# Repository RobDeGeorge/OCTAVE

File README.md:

<div align="center">

# OCTAVE

### The car head unit you build yourself.

**Live engine data. Gauges you design on the screen. Music that repaints the whole dash.<br>Your phone on the dash. A black box that remembers every drive.**

<sub>Real app, real UI, recorded from a script. Engine data comes from OCTAVE's built-in car simulator, so you can try all of this with no car.</sub>

**Windows · macOS · Linux · Raspberry Pi / Orange Pi · Android · your browser**

**Try it in your browser: https://robdegeorge.com/OCTAVE/** (the simulated car, no install, about 25 MB)

### [Download](https://github.com/RobDeGeorge/OCTAVE/releases/latest) &nbsp;·&nbsp; [Wiki](https://robdegeorge.com/OCTAVE/wiki/) &nbsp;·&nbsp; [Build your own frontend](https://robdegeorge.com/OCTAVE/wiki/writing-a-frontend.html) &nbsp;·&nbsp; [Frontend playground](https://robdegeorge.com/OCTAVE/playground.html)

</div>

---

Stock head units are locked boxes. Phone projection hides the car behind your phone. **OCTAVE is a full infotainment system you run on your own hardware**: a Pi behind the dash, a laptop in a project car, an old Android tablet. It reads the car over OBD-II, plays your music, mirrors your phone, and every pixel of it is yours to change.

I daily-drive it in my 2003 Jeep TJ.

> **Getting data from your car:** plug an ELM327 OBD-II adapter (the cheap $15–30 kind) into the port under your dash. Every car sold in the US since 1996 has one.
> - **USB** adapters work on every platform.
> - **Bluetooth** adapters pair from inside OCTAVE on Linux and the Pi. On Windows and macOS, pair it in system settings and pick its port.
> - **BLE** adapters work on Android.
>
> No car handy? `octave --sim` drives a simulated one, in any build.
>
> I am also designing an adapter for OCTAVE itself, every OBD-II protocol on one board: [an OBD adapter of its own](#an-obd-adapter-of-its-own). It is not built yet.

<table>
<tr>
<td width="33%" align="center"><br><b>Music paints the dash</b><br><sub>Every song recolours the UI</sub></td>
<td width="33%" align="center"><br><b>Gauges you design</b><br><sub>On the screen or in a browser, 129 live readings</sub></td>
<td width="33%" align="center"><br><b>A black box</b><br><sub>Every drive recorded, charted and compared</sub></td>
</tr>
<tr>
<td align="center"><br><b>Your phone on the dash</b><br><sub>Android over USB or Wi-Fi, iPhone over AirPlay</sub></td>
<td align="center"><br><b>Shift light & codes</b><br><sub>Read and clear the check-engine light</sub></td>
<td align="center"><br><b>Open API</b><br><sub>Drive it from a browser or a script</sub></td>
</tr>
<tr>
<td align="center"><br><b>The car in 3D</b><br><sub>Doors, lights and tilt, live</sub></td>
<td align="center"><br><b>Your own screen</b><br><sub>Swap the whole UI for one you wrote</sub></td>
<td align="center"><br><b>Its own OBD adapter</b><br><sub>Designed here, not built yet</sub></td>
</tr>
</table>

---

## Music that paints the whole dash

Skip a track and the whole interface takes its colours from the cover art. Local MP3, M4A and FLAC with a live waveform.

## Gauges you design on the screen

**129 live readings** (121 OBD-II PIDs plus the IMU), **13 widget types**, and full-screen dashboards you swipe between. Pick one of the built-ins or build your own:

No code and no JSON. Start from a template that fills itself in with what your car reports, then select a gauge and drag it: the others move out of the way. The gallery shows every widget running on live data, the picker lists your car's readings by system, and one sheet per gauge covers its look, range and warning limits, with a test value to watch them trip. Undo, redo, three grid densities, and a portrait layout of its own. Share a dashboard as a file or through the clipboard.

Rather use a keyboard? The head unit serves the same editor to a browser (**Dashboards > In a browser** shows the address, a QR code and a pairing code), and what you change there previews live on the car's screen:

A dashboard can also watch the car for you: a red strip across the top when one of its values goes critical, or a rule that brings it up by itself, such as the temperatures when the coolant runs hot.

Screen mounted upright, or running on a phone? Home and every dashboard re-flow for portrait.

<p align="center">
  
  &nbsp;&nbsp;
  
</p>

## A black box for every drive

OCTAVE records **every reading of every drive**, quietly, in the background. Open Trip History to see each drive's distance, top speed, peak coolant, voltage and fuel used, and chart any parameter over the whole trip. Export a drive as CSV, or open the files yourself.

**Trends** lines your drives up against each other: warm-up time, running coolant temperature, idle and charging voltage, warm idle speed, fuel trims. When the recent drives move away from the earlier ones it says so, and what usually causes it. Here a thermostat is starting to stick open.

<sub>The history in these pictures is generated (`tools/trips/make_mock_trip.py`): 40 drives over two months with a thermostat wearing out.</sub>

## Shift light, warnings and trouble codes

Set your own RPM bands: the lamp goes green, flashes yellow, and at the top **the whole screen strobes red**, whatever page you're on. Any gauge can also be a warning light with its own threshold.

Check-engine light on? Read the stored and pending codes in plain English, grab the freeze frame, and clear them, right from the dash.

## Your phone on the dash

Plug in an Android phone, or pair it once over Wi-Fi by scanning a QR code. OCTAVE mirrors a DeX-style desktop onto the dash with its own built-in client: **nothing to install on the phone**. A bumped USB cable picks up where it left off instead of starting over.

**iPhone:** OCTAVE is an AirPlay receiver, so an iPhone mirrors its screen or plays its music to the dash the way it would to an Apple TV. AirPlay carries no touch, so the head unit also pairs with the phone as a Bluetooth mouse and your taps on the dash land on the phone. Linux and the Pi for now, and off until you turn it on.

**Android Auto** runs through Google's Desktop Head Unit, or through OCTAVE's own built-in receiver (beta, checked on desktop Linux so far).

## The car, live in 3D

A rigged model of the Jeep with working doors, hood, tailgate, lights, steering and wheels, rolled and pitched in real time by an IMU on the dash.

Pitch, roll, heading, a G-force plot with a trail, altitude and temperature, sampled at 200 Hz.

## Drive it from anything

<table>
<tr>
<td width="38%" align="center"></td>
<td>

Everything the touch screen can do is open to other programs over a small JSON API. Start OCTAVE with `--service --service-bind 0.0.0.0` and open **`http://<head-unit-ip>:9876/`** on your phone, enter the pairing code from Settings > Device > Service: live gauges, now playing, volume. Or run it with **no screen at all** (`--headless`) and make your own UI.

```python
from octave_client import Client

with Client() as octave:
    octave.call("nowPlaying", "next")
    octave.subscribe("paramStore", properties=["RPM", "SPEED"])
    for event in octave.events():
        print(event["values"])        # {'RPM': 2210, 'SPEED': 41}
```

[SDKs](sdk/) for Python, TypeScript and Go, a no-build [web client](sdk/web/index.html), [starter projects](templates/) to copy, the full [API reference](https://robdegeorge.com/OCTAVE/wiki/api-reference.html), and a walkthrough: **[Writing a Frontend](https://robdegeorge.com/OCTAVE/wiki/writing-a-frontend.html)**. Install your frontend as the head unit's screen from Settings > Device > Frontends; *Try* gives it two minutes, and five presses of mute always bring the built-in screen back.

**[Try a frontend in your browser](https://robdegeorge.com/OCTAVE/playground.html)** against the real core and a simulated car, or browse the **[frontend gallery](https://robdegeorge.com/OCTAVE/wiki/frontend-gallery.html)**: five complete examples in Svelte, Textual, Gio, SDL2 and egui (`examples/frontends/`, MIT). Built one? See [CONTRIBUTING.md](CONTRIBUTING.md).

</td>
</tr>
</table>

<p align="center"><sub>The five example frontends: Glass (Svelte), Sunlight (Go + Gio), Retro Cluster (Rust + egui), Arcade (C + SDL2), Console (Python + Textual). Each one is a complete screen for the same car.</sub></p>

## An OBD adapter of its own

The $20 ELM327 clones work, and they are the slow part of the system: every reading waits for a Bluetooth round trip, and they keep drawing current from a parked car. So OCTAVE is getting an adapter of its own, designed in this repository: [`hardware/obd-adapter/`](hardware/obd-adapter/).

- **Every OBD-II bus on one board:** two CAN channels, K-line (ISO 9141 / KWP2000) and J1850 VPW / PWM for older Chrysler, GM and Ford cars. My 2003 TJ speaks VPW, which a CAN-only dongle cannot hear at all.
- **An STM32G474 on the car's side, an ESP32 for the radio:** Bluetooth Classic, BLE and Wi-Fi, plus USB-C for a head unit on a cable.
- **Plugs straight into the port,** on a small J1962 plug board soldered across its end. Reverse-battery and surge protection on the way in; the supply is simulated to keep running through a 6 V cold crank.
- **Meant to do more than an ELM327.** The plan is the ELM327 command set for every app, plus a native mode: the adapter schedules the polling itself, stamps each sample as it comes off the bus, and keeps recording while Bluetooth is down, to fill the black box in afterwards.
- **A board written as code.** The schematic, placement, routing and fab files are generated by Python ([`gen/obd_adapter.py`](hardware/obd-adapter/gen/obd_adapter.py) is the design; `python3 build.py all` rebuilds everything through KiCad and Freerouting), and checked the same way: ERC and DRC clean, the STM32's pins against ST's own data, two datasheet audits, and ngspice simulations of the supply, the input protection and the K-line and J1850 circuits. Every finding and what was done about it is in [`verify/REVIEW.md`](hardware/obd-adapter/verify/REVIEW.md).

> **Where it stands:** Rev 0 is a bring-up board for the bench and the Jeep, not the final dongle. It is designed and routed, the fab files are generated, and bring-up firmware is started (it builds and passes its host tests; it has never run on hardware). **Nobody else has reviewed the board, and it has not been ordered or built.** Read it, learn from it, tell me what is wrong with it, but do not send it to a fab yet. Plan and background: [`TODO/diy-obd-adapter.md`](TODO/diy-obd-adapter.md). Nothing in OCTAVE depends on it: the ELM327 adapters above keep working.

---

## Install

Grab the file for your platform from **[Releases](https://github.com/RobDeGeorge/OCTAVE/releases/latest)**. No toolchain needed.

| Platform | File | |
|---|---|---|
| Windows | `OCTAVE-<version>-windows-x86_64.exe` | Run the installer |
| macOS | `OCTAVE-<version>-macos.dmg` | Drag to Applications |
| Linux | `OCTAVE-<version>-linux-x86_64.AppImage` | `chmod +x`, then run |
| Raspberry Pi / Orange Pi (64-bit) | `OCTAVE-<version>-linux-aarch64.AppImage` | `chmod +x`, then run |
| Android | `OCTAVE-<version>-android-arm64-v8a.apk` | Sideload it |

<details>
<summary>Platform notes</summary>

- **Linux:** Ubuntu 22.04+, Debian, Mint, Fedora, openSUSE and Arch. Arch may need `sudo pacman -S fuse2`, or run `./OCTAVE-*.AppImage --appimage-extract-and-run`.
- **Android:** each release APK is signed with its own key, so uninstall the previous version before updating.

</details>

## How it compares

| | OCTAVE | Crankshaft | OpenAuto Pro | Stock Android Auto |
|---|---|---|---|---|
| Open source | Yes, GPLv3 | Yes | partial | No |
| Works without a phone | Yes | No, AA projection | No, AA projection | No |
| Live OBD-II, your own dashboards | Yes | No | limited | No |
| Records every drive | Yes | No | No | No |
| Phone mirroring | Yes: Android with nothing to install, iPhone over AirPlay | AA only | AA only | n/a |
| Open API for your own UI | Yes | No | No | No |
| Fully themable / forkable UI | Yes, QML | limited | limited | No |
| Develop on your laptop | Yes, Win / macOS / Linux | Pi only | Pi only | n/a |

## Everything else it does

- **ESP32 wireless volume knob** with an LED ring that matches the theme
- **Gesture sensor** (PAJ7620U2): wave to skip, pause or change the volume
- **Bluetooth OBD adapters** found, paired and connected from the app on Linux; BLE adapters on Android
- **Spotify** (experimental): your playlists in the same song table as your own music, playing on the Spotify app on your phone (Premium)
- **Pick the audio output**: the car's amp, a USB DAC or Bluetooth, from Settings
- **The browser demo is the real app**: point it at a folder of your own music, or connect a real Bluetooth LE adapter from Chrome or Edge
- **100+ settings**, all on the screen, all saved
- **The whole wiki inside the app**, readable offline
- **Logs and crash traces** you can export from the dash when something goes wrong

---

## Hack on it

OCTAVE is C++ / Qt 6 with a QML frontend, built with CMake, small enough to fork. `--dev` runs it with a **simulated car** (warm-up, overheating and low-fuel scenarios) and simulated motion, so you can work on gauges at your desk.

<details>
<summary><b>Build from source</b></summary>

Qt 6.7+ and CMake 3.21+:

```bash
git clone https://github.com/RobDeGeorge/OCTAVE.git
cd OCTAVE
cmake -S . -B build -DCMAKE_BUILD_TYPE=Debug
cmake --build build -j8
./build/octave --dev                       # with the simulated car
ctest --test-dir build --output-on-failure # the test suite
```

Every platform and packaging target is in [BUILD.md](BUILD.md). The optional Python tools around the app (dev scripts, docs builders) install into a virtualenv next to the checkout:

```bash
python3 -m venv venv && venv/bin/pip install -r requirements.txt
```

Until October 2026 OCTAVE also had a Python / PySide6 backend. It is frozen, with its own wiki, on the [`python-final`](https://github.com/RobDeGeorge/OCTAVE/tree/python-final) branch.

</details>

<details>
<summary><b>Dev tooling: how the clips above were made</b></summary>

Every clip and picture in this README is scripted, and one command makes them all again. `./build/octave --dev --profile` (a Debug build) runs OCTAVE with the simulator and a local command server; a story script drives it scene by scene (navigate, play, floor the throttle, tap buttons by their label, type into fields, build a dashboard), captures the window from inside Qt, and writes WebP and PNG. The same run fills the black box with two months of mock drives, shoots the browser pages in headless Chromium, renders the adapter board with `kicad-cli` from the committed design, and then checks that every picture this file points at exists. The same channel is exposed as MCP tools, so a coding agent can drive the app, change settings, read performance counters and record clips. The in-app half is in `src/dev/`; see the [Development guide](https://robdegeorge.com/OCTAVE/wiki/development.html).

</details>

## What's next

- **The OBD adapter as a real board**: a review, a first order, and the firmware on hardware ([plan](TODO/diy-obd-adapter.md))
- **Android on the Play Store**: the APK runs today as a sideload ([plan](TODO/android-cpp-port.md))
- **Wireless CarPlay / Android Auto** through a CarlinKit dongle ([plan](TODO/carlinkit-dongle-port.md))
- **Video over the API**, so your own frontend can show the phone mirror too ([plan](TODO/open-backend.md))

Every plan lives in [`TODO/`](TODO/).

## Documentation

The **[wiki](https://robdegeorge.com/OCTAVE/wiki/)** covers the architecture, every manager and page, every setting, hardware setup and the build guides. The same pages ship in [`wiki/`](wiki/index.html) and inside the app. Building gauges: [`docs/GAUGE_AUTHORING.md`](docs/GAUGE_AUTHORING.md). Building a frontend: [Writing a Frontend](https://robdegeorge.com/OCTAVE/wiki/writing-a-frontend.html) and [`docs/api/`](docs/api/README.md).

## Contributing

Pull requests and bug reports are welcome. Built a dashboard, a sensor integration, a port to new hardware, or your own frontend? Open an issue or a PR. I'd love to see it.

<details>
<summary><b>Built with</b></summary>

OCTAVE stands on a lot of other people's work.

**C++ app (every release binary)**

| Library | Used for |
|---|---|
| [Qt 6](https://www.qt.io/) (Core, Gui, Qml, Quick, Quick Controls 2, Multimedia, Network, Concurrent, SerialPort, Bluetooth) | The whole application: UI, audio playback, networking, serial and Bluetooth OBD |
| Qt Quick 3D, Quick 3D Asset Utils, Quick Timeline | The 3D Jeep and the music-device scenes |
| Qt DBus | BlueZ pairing on Linux |
| Qt WebEngine / Qt WebView | The offline wiki reader (desktop / Android) |
| Qt Sensors | The phone's motion sensors on Android |
| [TagLib](https://taglib.org/) | Reading tags and embedded album art |
| [FFmpeg](https://ffmpeg.org/) (libavcodec, libavutil) | Decoding the phone mirror's H.264 stream |
| [SQLite](https://sqlite.org/) | The black box (compiled in from `third_party/sqlite/`) |
| [OpenSSL](https://www.openssl.org/) | The built-in Android Auto receiver's encryption; the AirPlay receiver |
| [libplist](https://libimobiledevice.org/) | The AirPlay receiver (Linux), with FFmpeg and OpenSSL |
| [CMake](https://cmake.org/) | Build system |

**Python helper tools (optional, `requirements.txt`)**

| Package | Used for |
|---|---|
| [MCP Python SDK](https://github.com/modelcontextprotocol/python-sdk), [Pillow](https://python-pillow.org/), [mss](https://github.com/BoboTiG/python-mss), [NumPy](https://numpy.org/), [psutil](https://github.com/giampaolo/psutil) | Dev tooling: MCP servers, screenshots and clips, perf scripts |
| [python-OBD](https://github.com/brendan-w/python-OBD) | Dev scripts for reading and clearing trouble codes |
| [Ruff](https://docs.astral.sh/ruff/) | Lint |

**Android**

| Library | Used for |
|---|---|
| Qt for Android, Gradle, Android SDK / NDK | Building the APK |
| [OpenSSL](https://www.openssl.org/) | HTTPS for Qt Network (`android/openssl/`) |

**Code bundled in this repository**

| Component | License | Where |
|---|---|---|
| [scrcpy](https://github.com/Genymobile/scrcpy) server, forked at v3.3.4 | Apache 2.0 | `phone_server/`, prebuilt jar in `tools/phone-server/` |
| [UxPlay](https://github.com/FDH2/UxPlay)'s AirPlay library, 1.74 | LGPL 2.1+, with GPL 3.0 and MIT parts (see its README) | `third_party/uxplay/` |
| [QR Code generator library](https://www.nayuki.io/page/qr-code-generator-library) by Project Nayuki | MIT | `src/phone_mirror/qrcodegen.*` |
| Android platform-tools (`adb`) | See its `NOTICE.txt` | `tools/platform-tools/` |

**External tools and services:** adb (phone mirroring and Android Auto), Google's Android Auto Desktop Head Unit (the Android Auto view).

**The OBD adapter (`hardware/obd-adapter/`):** [KiCad](https://www.kicad.org/) (the project, `kicad-cli` checks, fab output and the renders above), [Freerouting](https://github.com/freerouting/freerouting) (autorouting), [ngspice](https://ngspice.sourceforge.io/) (simulations), `arm-none-eabi-gcc` (firmware).

**Fonts, icons and 3D assets**

- **[Google Sans](https://fonts.google.com/)**: UI typeface. **[JetBrains Mono](https://www.jetbrains.com/lp/mono/)**: monospace readouts.
- **OCTAVE Symbols**: a subset of [Noto Sans Symbols and Noto Sans Symbols 2](https://fonts.google.com/noto) (SIL OFL), renamed as the OFL requires, built by `tools/fonts/build_symbol_font.py` with [fontTools](https://github.com/fonttools/fonttools).
- **Icons**: original SVGs drawn for OCTAVE (Illustrator sources in `frontend/assets/-src/`).
- **The 2003 Jeep TJ**: an original model, built procedurally in [Blender](https://www.blender.org/) by `tools/vehicle/build_jeep_tj.py` from photos of one real TJ; no third-party meshes or textures ([details](tools/vehicle/README.md)).
- **Record player, cassette deck, CD player, iPod and friends**: original glTF models generated by `tools/music_devices/generate.py` (NumPy, Pillow).
- **Studio lighting (`.hdr`)**: generated by `tools/vehicle/build_studio_probe.py`.

**CI and packaging:** [GitHub Actions](https://github.com/features/actions) with [install-qt-action](https://github.com/jurplel/install-qt-action), [setup-android](https://github.com/android-actions/setup-android) and [action-gh-release](https://github.com/softprops/action-gh-release); [vcpkg](https://vcpkg.io/) and [Homebrew](https://brew.sh/) for TagLib and FFmpeg; [Inno Setup](https://jrsoftware.org/isinfo.php) for the Windows installer; [linuxdeploy](https://github.com/linuxdeploy/linuxdeploy) with its Qt plugin for the AppImages; `windeployqt`, `macdeployqt` and `androiddeployqt` from Qt.

</details>

## License

Copyright 2026 Rob DeGeorge.

OCTAVE is free software: you can redistribute it and/or modify it under the terms of the GNU General Public License as published by the Free Software Foundation, either version 3 of the License, or (at your option) any later version. It is distributed in the hope that it will be useful, but WITHOUT ANY WARRANTY; without even the implied warranty of MERCHANTABILITY or FITNESS FOR A PARTICULAR PURPOSE. See [LICENSE](LICENSE) for the full text.

The service clients (`sdk/`), starter projects (`templates/`) and example frontends (`examples/frontends/`) are MIT, so a frontend you build on them can use any license ([Your Frontend, Your License](wiki/writing-a-frontend.html#license)).

Code published before 2026-10-12 (v0.9.4 and earlier) was released under the MIT License and remains available under those terms.

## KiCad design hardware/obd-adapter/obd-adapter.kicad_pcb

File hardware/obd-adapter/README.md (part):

# OCTAVE OBD adapter, Rev 0 (bring-up board)

Our own OBD-II adapter: STM32G474 (vehicle side) + ESP32 (Bluetooth Classic SPP, BLE, Wi-Fi), every OBD-II bus, USB-C. Rev 0 is a bring-up board for the bench and the Jeep, not the final dongle. It has room to probe, test points and header access to spare pins, and it plugs straight into the car's OBD-II port. Plan and background: `TODO/diy-obd-adapter.md`.

**Status:** generated, then verified: an STM32 pin check against ST's pin data, two independent datasheet audits and ngspice simulations. Every finding is fixed or accepted, see `verify/REVIEW.md`. Not yet reviewed by a human, not ordered. Read "Before ordering" below.

**The main board is routed** (2026-11-10): 0 DRC errors, 0 unconnected pads, schematic and board agree. `gen/routing.json`, `obd-adapter.kicad_pcb`, `drc.rpt` and everything in `fab/` are that board, with the changes of 2026-11-09 in it (the buck loop, the parked-watch parts, the microSD, the mounting holes, `verify/REVIEW.md` rounds 5 to 7). The route is the autorouter's, finished by hand round the STM32; it has passed the rule check, not a person's eye. Later the same day (`verify/REVIEW.md` round 8): the crystal's tracks and the CAN1 pair were re-laid by hand, and six BOM lines moved to parts from JLCPCB's no-fee libraries, which changed four values round the buck (RT 160k, feedback 68k / 12k, 47 pF on COMP).

## Files

| Path | What |
|---|---|
| `gen/obd_adapter.py` | **The design.** Every part, its LCSC number and its pin-to-net map. Edit this, not the KiCad files. |
| `gen/parts.py` | LCSC part numbers, checked against JLCPCB's parts library on 2026-11-02, 2026-11-09 and 2026-11-10. |
| `gen/layout.py` | Board placement: fixed positions for the parts whose position matters, block regions for the rest. |
| `gen/libdefs.py` | Project symbols KiCad doesn't ship (SOIC-8 N-MOSFET, TPS22918, CH340C, LIS2DH12), with the pinouts checked against the datasheets, and the two plug footprints (drawn by `gen/mklib.py`). |
| `gen/build.py` | Regenerates everything (see below). |
| `obd-adapter.kicad_sch` / `.kicad_pcb` | Generated KiCad 10 project. Open it in KiCad to review. |
| `gen/plugprint.py` | Draws the 1:1 print of the plug's adapter board from its `.kicad_pcb` (run by `build.py fab`). |
| `fab/` | Generated: Gerber zips, JLCPCB BOM + CPL, hand-fit list, and `obd-adapter-plug-rev0-print-1to1.pdf`, the sheet to try a bought plug on. |
| `firmware/` | Bring-up firmware for the STM32 (bare-metal C, CMake + `arm-none-eabi-gcc`): reset-safe pins, clock, a serial console, battery voltage, I2C scan, CAN listen-only, K-line. Builds for the board and for a NUCLEO-G474RE; **not yet run on hardware**. See `firmware/README.md`. |
| `verify/` | Pre-fab verification: `REVIEW.md` (every finding and its fix), the STM32 pin check, the ngspice sims and plots. |

```bash
cd hardware/obd-adapter/gen
python3 build.py sch      # project symbols, schematic, ERC (kicad-cli)
python3 build.py pcb      # board with placement (pcbnew Python API)
python3 build.py route    # Freerouting autoroute, GND pours, DRC with schematic parity
python3 build.py fab      # Gerbers, drill, BOM, CPL
python3 build.py all
```

Use the system `python3` (KiCad's `pcbnew` module lives there), not the repo venv. Tools: KiCad 10, Java, and the Freerouting 2.5 jar (`~/.local/share/freerouting/freerouting-2.5.0.jar`, or set `FREEROUTING_JAR`). 2.2 loops forever on this board.

`build.py route` replays the frozen routing (`gen/routing.json`) and refuses if parts moved. To route again:

- `OBD_REROUTE=patch python3 build.py route`: keeps the frozen routing, drops only the copper over parts that moved (or in a DRC clash) and routes the gaps. Minutes, for small placement changes.
- `OBD_REROUTE=1 python3 build.py route`: a full route from scratch. About 4 hours for the board as it is now, and it will not finish by itself: see "How the board is routed" before throwing the frozen route away.

Before a full route, check the placement in seconds: `python3 precheck.py` (DRC with the hand-laid power copper in place) and `python3 congestion.py` (a routing-density estimate; keep `peak` ≤ 0.55 and `p95` ≤ 0.33, the levels this board has routed clean at). `OBD_W` / `OBD_H` try another board size, `OBD_TWO_SIDED=1` puts the small parts on the bottom.

The schematic and the board are generated from the same netlist, and `kicad-cli pcb drc --schematic-parity` checks that they agree. Every pin on the schematic is joined by net label, so a net is everything that carries the same name. The sheet (A0) spaces each part by what it really takes up, labels and text included, and `build.py sch` stops if any two pieces of text touch. **Do not hand-edit the generated files**: the next build overwrites them. The exceptions are copper and labels: after routing by hand in KiCad, run `build.py freeze` so the next build replays your tracks, and copy any reference-label moves into `LABELS` in `gen/layout.py`.

## Blocks

**MCU: STM32G474RET6.** A 16 MHz crystal (for FDCAN timing), SWD on a 2x5 1.27 mm header, RESET / USER buttons, R/G/B LEDs and a 4-way `CONFIG` DIP switch (SW6): 1 ESP_ON, 2 / 3 the CAN1 / CAN2 120 Ω terminations, 4 BOOT0. All off in the car. VDDA / VREF+ are on 3V3 with their own 100 nF + 1 µF (no ferrite bead: the ADC only reads the battery divider). The USER button (PA15) and `KLINE_RX` (PC0) have no pull-up resistor; firmware uses the pins' own.

**Power:** J1962 pin 16 → 2 A 60 V PTC (2920L200/60) → 5.0SMDJ26CA → LM74700 ideal diode + AO4264E → `VBAT_P` (with 47 µF bulk).
- `VBAT_P` feeds a TPS54360B buck (60 V input; the datasheet's 600 kHz design with the output set to 5.33 V), then an SS34 diode-OR with USB VBUS (`5V` ≈ 4.9 V), then an AP2114H 3.3 V LDO (SOT-223).
- The buck's EN divider is not fitted, so the internal UVLO keeps it running through a 6 V cold crank. A cycle-by-cycle simulation (`verify/sim/sim_buck_sw.py`, `verify/REVIEW.md` round 8) has `5V_BUCK` unmoved through that crank, regulating down to 5.6 V at the plug, with under 9 mV of ripple from 9 to 42 V and 131 mV of dip on a 0.1 to 1.0 A load step.
- **To check on the first board:** the buck's SW node with 6 to 7 V on the plug and 0.5 to 1 A drawn from 5 V. Alternating pulse widths would mean the part's internal slope compensation (not published) is short for 8.2 µH at that duty cycle; a 10 or 15 µH inductor in the same footprint is the fix (`verify/REVIEW.md` #71).
- The ESP32 has its own TPS22918 load switch, placed at the module's 3V3 pin. Its ON pin is a diode OR of `ESP_PWR_EN` (PB6, off at reset) and `VBUS2` (the ESP32's USB port), so plugging into J7 always powers the ESP32. CONFIG switch 1 (`ESP_ON`) also powers it without STM32 firmware, by pulling the PB6 net to 3V3 through 1k (R70); turn it off again for normal use. Firmware that drives PB6 low with the switch left on wastes 3.3 mA and the ESP32 stays off.
- A 1k bleed (R69) holds `VBUS2` at ground while J7 is unplugged. Without it the reverse leakage of J7's SS34 (up to 0.4 mA in a hot car) raised the load switch's ON pin and the ESP32 switched itself on.
- The ideal diode (U6 LM74700 driving Q1, an AO4264E 60 V FET) blocks a reversed battery and holds `VBAT_P` up through a negative pulse, for about 20 mV where a diode costs 0.3 V. A B560C Schottky in its place was tried on 2026-11-09 (three parts and 80 µA of parked current less) and taken out again: with the battery reversed its leakage pulled `VBAT_P` to −0.7 V at 100 °C, past the buck's −0.3 V rating, and it took 0.3 V off the cranking headroom (`verify/REVIEW.md` #54, `verify/sim/sim_input_d29.py`). The battery-voltage divider is ahead of it, on `VBAT_F`.
- The TVS is bidirectional on purpose. A unidirectional one would conduct into a reversed battery and defeat the ideal diode.
- Everything on `VBAT_P` must survive the TVS's ~42 V clamp.

**DLC_SW:** a switched battery rail (SI2309CDS P-MOSFET high side, `DLC_SW_EN` = PC3). It feeds the J1850 supply, the LM2901 (through 470 Ω and a 33 V zener) and the K/L 510 Ω pull-ups (through 1N4148W, so the car's own pull-up cannot back-feed the rail while it is off). ScanTool's STN datasheets warn that pull-ups left on the battery draw sleep current and can disturb the bus, up to stalling an engine.

**J1850 VPW / PWM:** STN-style discrete circuit, adapted from the STN1110/1170/21xx reference schematics (3.3 V parts like ours).
- **Supply:** LM317L with 240 / 680 / 470 Ω gives 7.24 V for VPW. A 2N7002 on `J1850_VSEL` (PB2) shorts the 470 Ω for 4.79 V (PWM).
- **Bus+:** 2N7002 → AO3401A → Schottky, with a 10k + Schottky bus load.
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
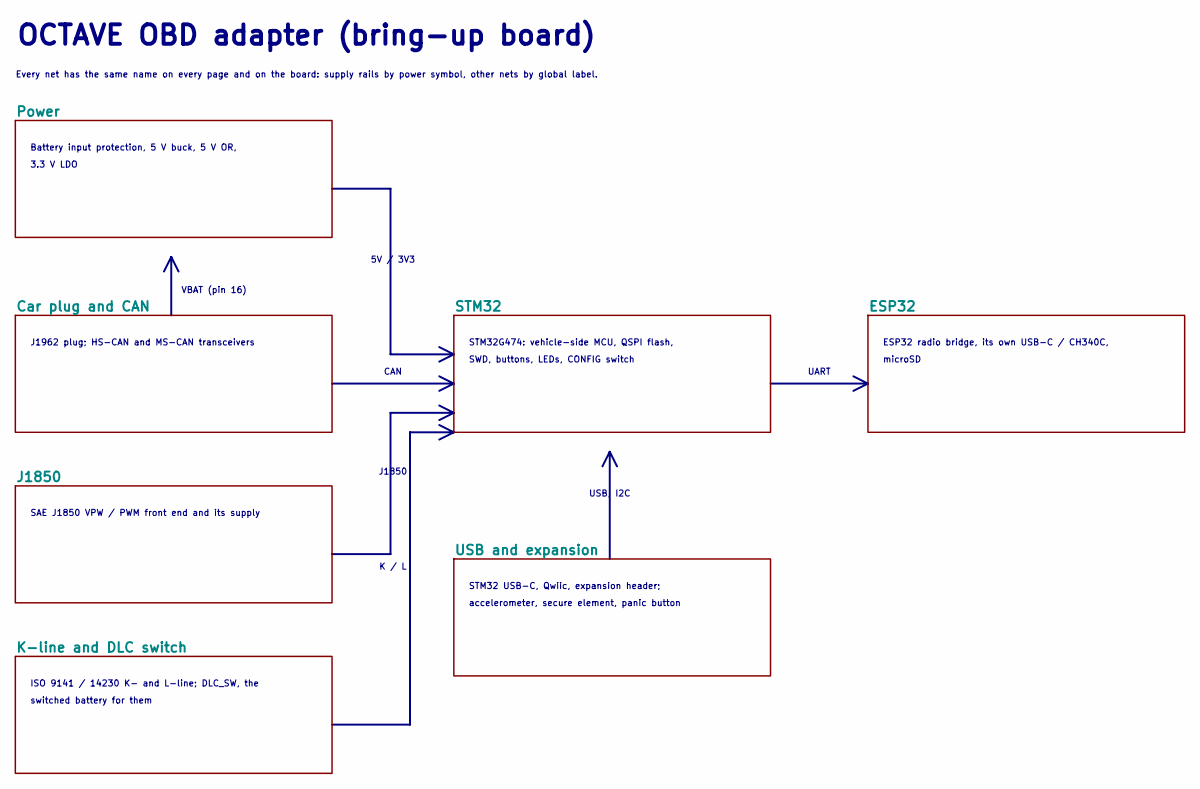
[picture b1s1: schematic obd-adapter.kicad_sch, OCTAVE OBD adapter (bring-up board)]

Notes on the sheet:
Battery input protection, 5 V buck, 5 V OR,
3.3 V LDO
J1962 plug; HS-CAN and MS-CAN transceivers
SAE J1850 VPW / PWM front end and its supply
ISO 9141 / 14230 K- and L-line; DLC_SW, the
switched battery for them
STM32G474: vehicle-side MCU, QSPI flash,
SWD, buttons, LEDs, CONFIG switch
ESP32 radio bridge, its own USB-C / CH340C,
microSD
STM32 USB-C, Qwiic, expansion header;
accelerometer, secure element, panic button
VBAT (pin 16)
5V / 3V3
CAN
J1850
K / L
UART
USB, I2C
OCTAVE OBD adapter (bring-up board)
Every net has the same name on every page and on the board: supply rails by power symbol, other nets by global label.

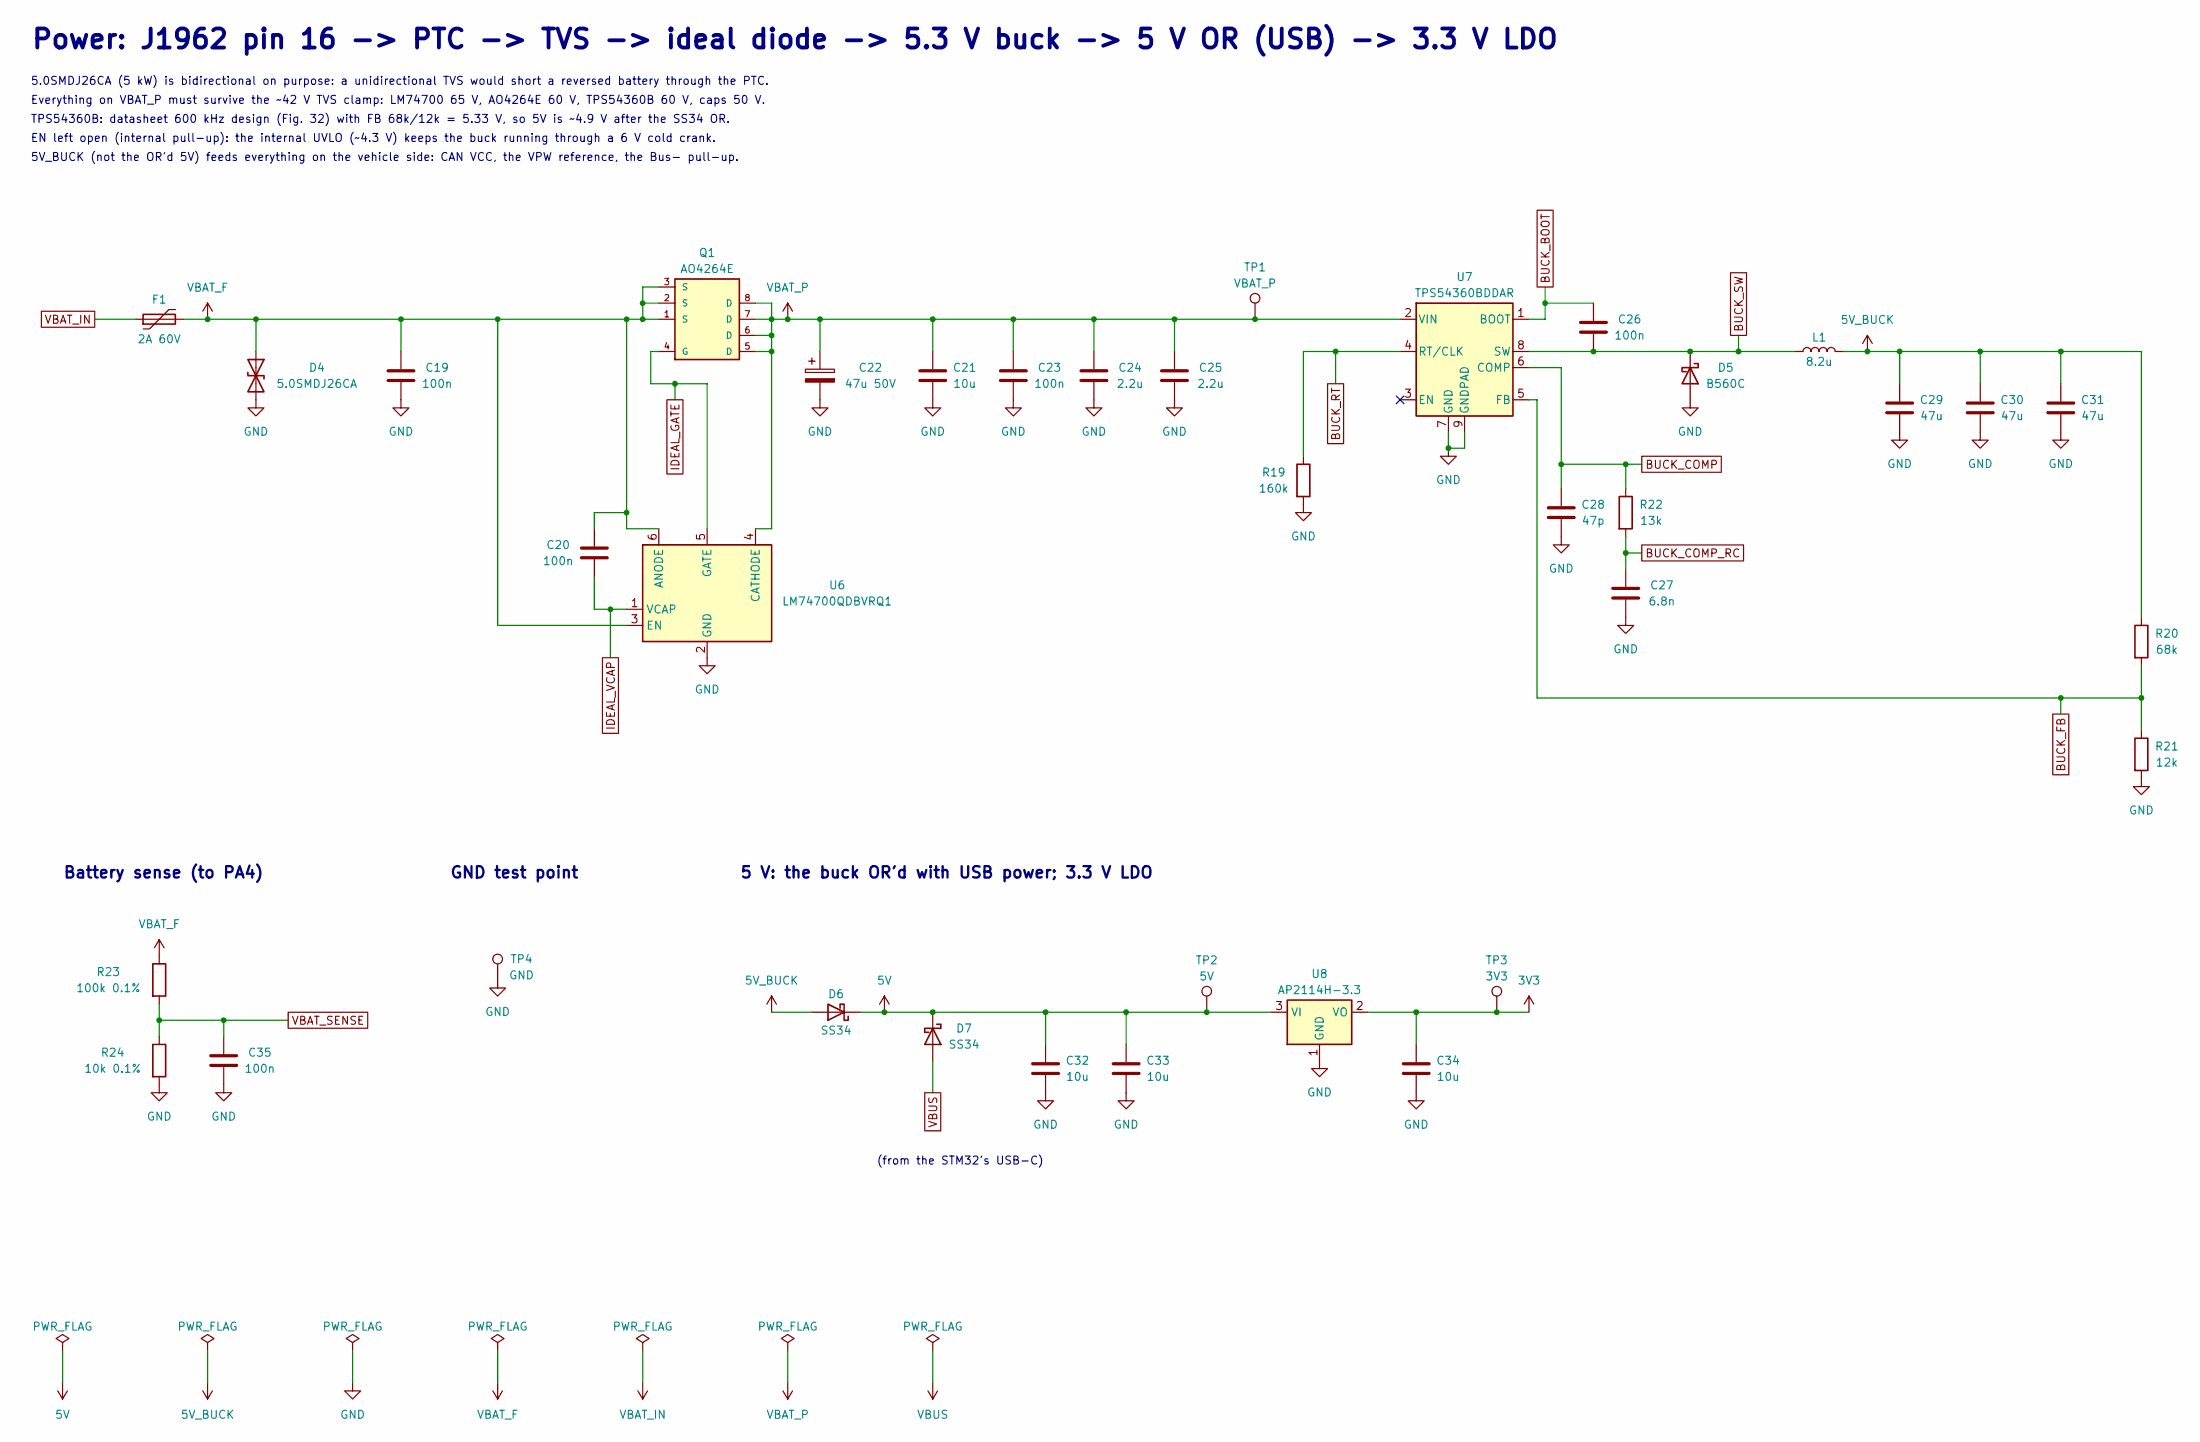
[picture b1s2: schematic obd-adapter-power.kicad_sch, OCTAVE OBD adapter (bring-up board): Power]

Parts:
C19, C20, C23, C26, C35: 100n; C_0603_1608Metric; LCSC C14663
C21: 10u; C_1206_3216Metric; LCSC C13585
C22: 47u 50V; CP_Elec_6.3x7.7; LCSC C2887275
C24, C25: 2.2u; C_1206_3216Metric; LCSC C50254
C27: 6.8n; C_0603_1608Metric; LCSC C1631
C28: 47p; C_0603_1608Metric; LCSC C1671
C29, C30, C31: 47u; C_1206_3216Metric; LCSC C96123
C32, C33, C34: 10u; C_0603_1608Metric; LCSC C96446
D4: 5.0SMDJ26CA; D_SMC; LCSC C444401
D5: B560C; D_SMC; LCSC C85100
D6, D7: SS34; D_SMA; LCSC C8678
F1: 2A 60V; Fuse_2920_7451Metric; LCSC C49326266
L1: 8.2u; L_Changjiang_FNR8065S; LCSC C96978
Q1: AO4264E; SOIC-8_3.9x4.9mm_P1.27mm; LCSC C334232
R19: 160k; R_0603_1608Metric; LCSC C22813
R20: 68k; R_0603_1608Metric; LCSC C23231
R21: 12k; R_0603_1608Metric; LCSC C22790
R22: 13k; R_0603_1608Metric; LCSC C22797
R23: 100k 0.1%; R_0603_1608Metric; LCSC C122538
R24: 10k 0.1%; R_0603_1608Metric; LCSC C95204
TP1: VBAT_P; TestPoint_Pad_D1.5mm
TP2: 5V; TestPoint_Pad_D1.5mm
TP3: 3V3; TestPoint_Pad_D1.5mm
TP4: GND; TestPoint_Pad_D1.5mm
U6: LM74700QDBVRQ1; SOT-23-6; LCSC C2941042
U7: TPS54360BDDAR; TI_SO-PowerPAD-8_ThermalVias; LCSC C524806
U8: AP2114H-3.3; SOT-223-3_TabPin2; LCSC C150716

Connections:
3V3: C34.1, TP3.1, U8.2 (VO); also elsewhere on the board
5V: C32.1, C33.1, D6.1 (K), D7.1 (K), TP2.1, U8.3 (VI); also elsewhere on the board
5V_BUCK: C29.1, C30.1, C31.1, D6.2 (A), L1.2, R20.1; also elsewhere on the board
BUCK_BOOT: C26.1, U7.1 (BOOT)
BUCK_COMP: C28.1, R22.1, U7.6 (COMP)
BUCK_COMP_RC: C27.1, R22.2
BUCK_FB: R20.2, R21.1, U7.5 (FB)
BUCK_RT: R19.1, U7.4 (RT/CLK)
BUCK_SW: C26.2, D5.1 (K), L1.1, U7.8 (SW)
GND: C19.2, C21.2, C22.2, C23.2, C24.2, C25.2, C27.2, C28.2, C29.2, C30.2, C31.2, C32.2, C33.2, C34.2, C35.2, D4.2 (A2), D5.2 (A), R19.2, R21.2, R24.2, TP4.1, U6.2 (GND), U7.7 (GND), U7.9 (GNDPAD), U8.1 (GND); also elsewhere on the board
IDEAL_GATE: Q1.4 (G), U6.5 (GATE)
IDEAL_VCAP: C20.1, U6.1 (VCAP)
VBAT_F: C19.1, C20.2, D4.1 (A1), F1.2, Q1.1 (S), Q1.2 (S), Q1.3 (S), R23.1, U6.3 (EN), U6.6 (ANODE)
VBAT_IN: F1.1; also elsewhere on the board
VBAT_P: C21.1, C22.1, C23.1, C24.1, C25.1, Q1.5 (D), Q1.6 (D), Q1.7 (D), Q1.8 (D), TP1.1, U6.4 (CATHODE), U7.2 (VIN); also elsewhere on the board
VBAT_SENSE: C35.1, R23.2, R24.1; also elsewhere on the board
VBUS: D7.2 (A); also elsewhere on the board

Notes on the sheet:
Power: J1962 pin 16 -> PTC -> TVS -> ideal diode -> 5.3 V buck -> 5 V OR (USB) -> 3.3 V LDO
5.0SMDJ26CA (5 kW) is bidirectional on purpose: a unidirectional TVS would short a reversed battery through the PTC.
Everything on VBAT_P must survive the ~42 V TVS clamp: LM74700 65 V, AO4264E 60 V, TPS54360B 60 V, caps 50 V.
TPS54360B: datasheet 600 kHz design (Fig. 32) with FB 68k/12k = 5.33 V, so 5V is ~4.9 V after the SS34 OR.
EN left open (internal pull-up): the internal UVLO (~4.3 V) keeps the buck running through a 6 V cold crank.
5V_BUCK (not the OR'd 5V) feeds everything on the vehicle side: CAN VCC, the VPW reference, the Bus- pull-up.
5 V: the buck OR'd with USB power; 3.3 V LDO
(from the STM32's USB-C)
Battery sense (to PA4)
GND test point

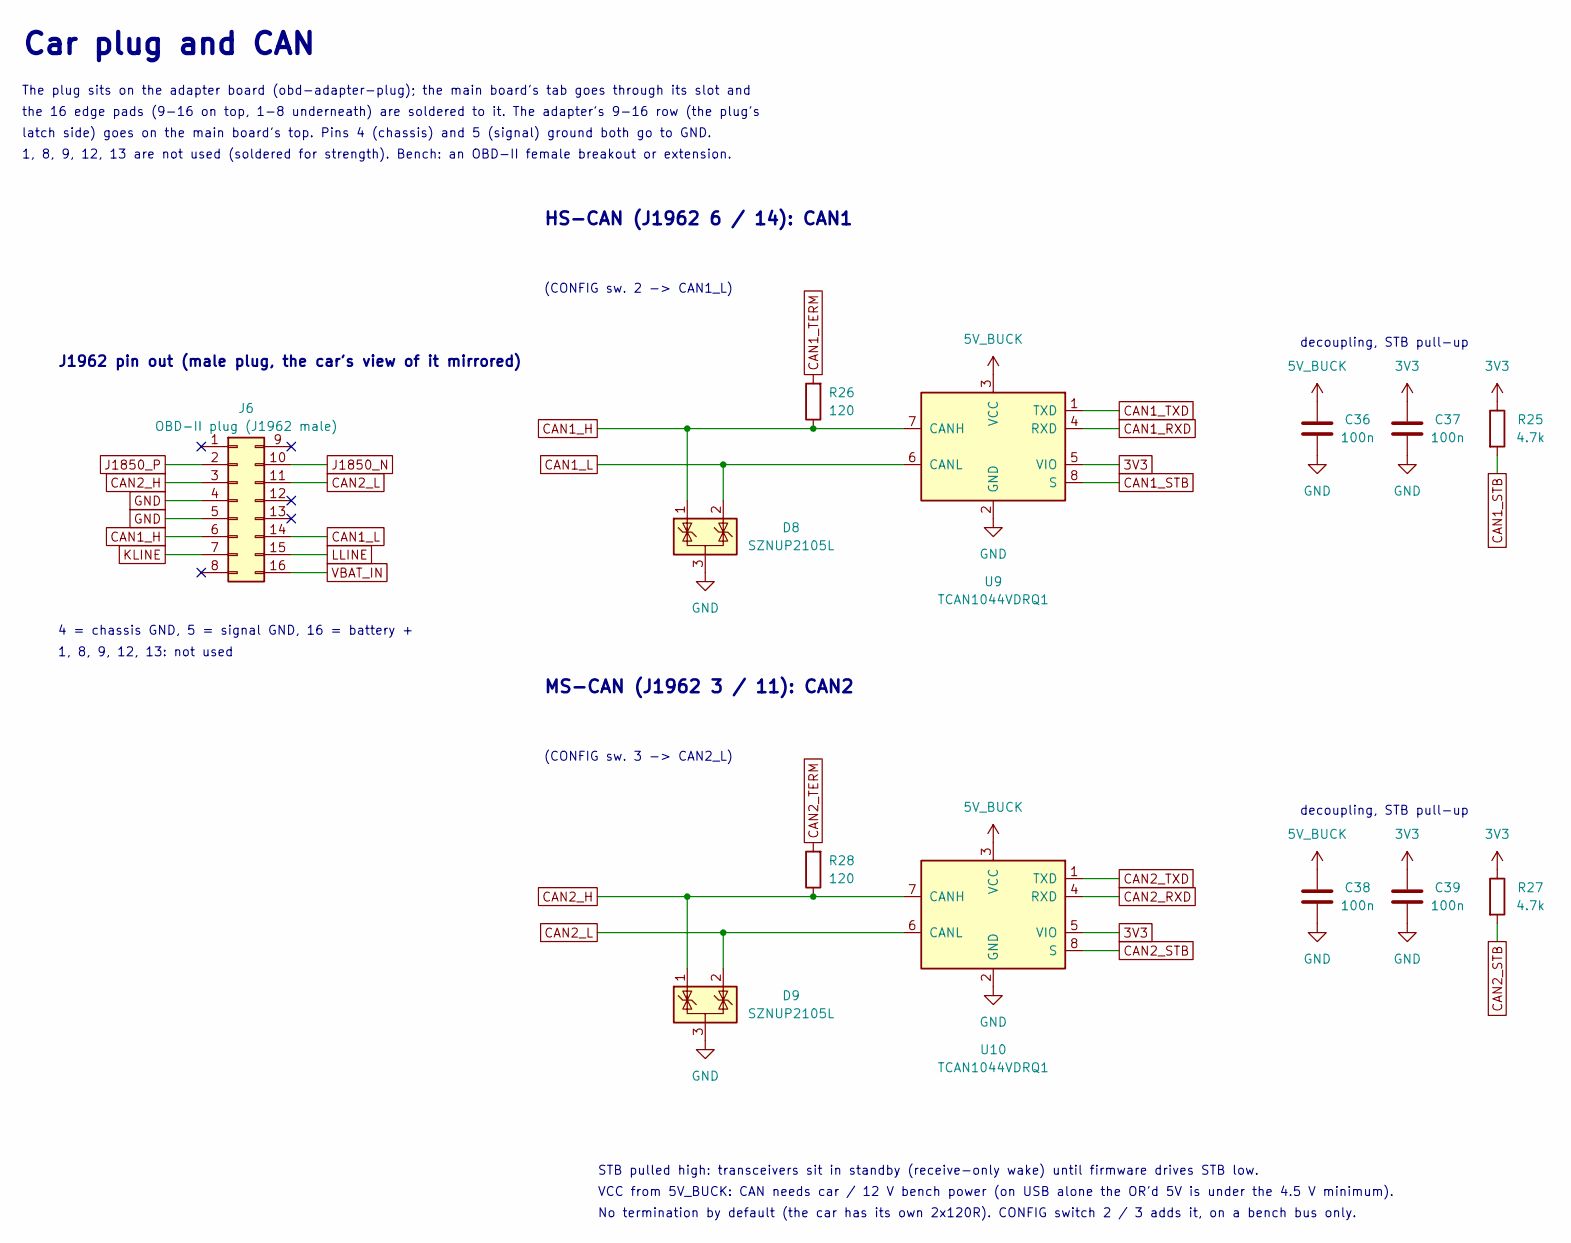
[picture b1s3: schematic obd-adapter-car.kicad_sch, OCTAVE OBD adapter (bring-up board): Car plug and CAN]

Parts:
C36, C37, C38, C39: 100n; C_0603_1608Metric; LCSC C14663
D8, D9: SZNUP2105L; SOT-23; LCSC C233494
J6: OBD-II plug (J1962 male); J1962_Edge_Joint
R25, R27: 4.7k; R_0603_1608Metric; LCSC C23162
R26, R28: 120; R_0603_1608Metric; LCSC C22787
U9, U10: TCAN1044VDRQ1; SOIC-8_3.9x4.9mm_P1.27mm; LCSC C1852061

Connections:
3V3: C37.1, C39.1, R25.1, R27.1, U9.5 (VIO), U10.5 (VIO); also elsewhere on the board
5V_BUCK: C36.1, C38.1, U9.3 (VCC), U10.3 (VCC); also elsewhere on the board
CAN1_H: D8.1 (K), J6.6, R26.1, U9.7 (CANH)
CAN1_L: D8.2 (K), J6.14, U9.6 (CANL); also elsewhere on the board
CAN1_RXD: U9.4 (RXD); also elsewhere on the board
CAN1_STB: R25.2, U9.8 (S); also elsewhere on the board
CAN1_TERM: R26.2; also elsewhere on the board
CAN1_TXD: U9.1 (TXD); also elsewhere on the board
CAN2_H: D9.1 (K), J6.3, R28.1, U10.7 (CANH)
CAN2_L: D9.2 (K), J6.11, U10.6 (CANL); also elsewhere on the board
CAN2_RXD: U10.4 (RXD); also elsewhere on the board
CAN2_STB: R27.2, U10.8 (S); also elsewhere on the board
CAN2_TERM: R28.2; also elsewhere on the board
CAN2_TXD: U10.1 (TXD); also elsewhere on the board
GND: C36.2, C37.2, C38.2, C39.2, D8.3 (A), D9.3 (A), J6.4, J6.5, U9.2 (GND), U10.2 (GND); also elsewhere on the board
J1850_N: J6.10; also elsewhere on the board
J1850_P: J6.2; also elsewhere on the board
KLINE: J6.7; also elsewhere on the board
LLINE: J6.15; also elsewhere on the board
VBAT_IN: J6.16; also elsewhere on the board

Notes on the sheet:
Car plug and CAN
The plug sits on the adapter board (obd-adapter-plug); the main board's tab goes through its slot and
the 16 edge pads (9-16 on top, 1-8 underneath) are soldered to it. The adapter's 9-16 row (the plug's
latch side) goes on the main board's top. Pins 4 (chassis) and 5 (signal) ground both go to GND.
1, 8, 9, 12, 13 are not used (soldered for strength). Bench: an OBD-II female breakout or extension.
J1962 pin out (male plug, the car's view of it mirrored)
4 = chassis GND, 5 = signal GND, 16 = battery +
1, 8, 9, 12, 13: not used
HS-CAN (J1962 6 / 14): CAN1
(CONFIG sw. 2 -> CAN1_L)
decoupling, STB pull-up
MS-CAN (J1962 3 / 11): CAN2
(CONFIG sw. 3 -> CAN2_L)
STB pulled high: transceivers sit in standby (receive-only wake) until firmware drives STB low.
VCC from 5V_BUCK: CAN needs car / 12 V bench power (on USB alone the OR'd 5V is under the 4.5 V minimum).
No termination by default (the car has its own 2x120R). CONFIG switch 2 / 3 adds it, on a bench bus only.

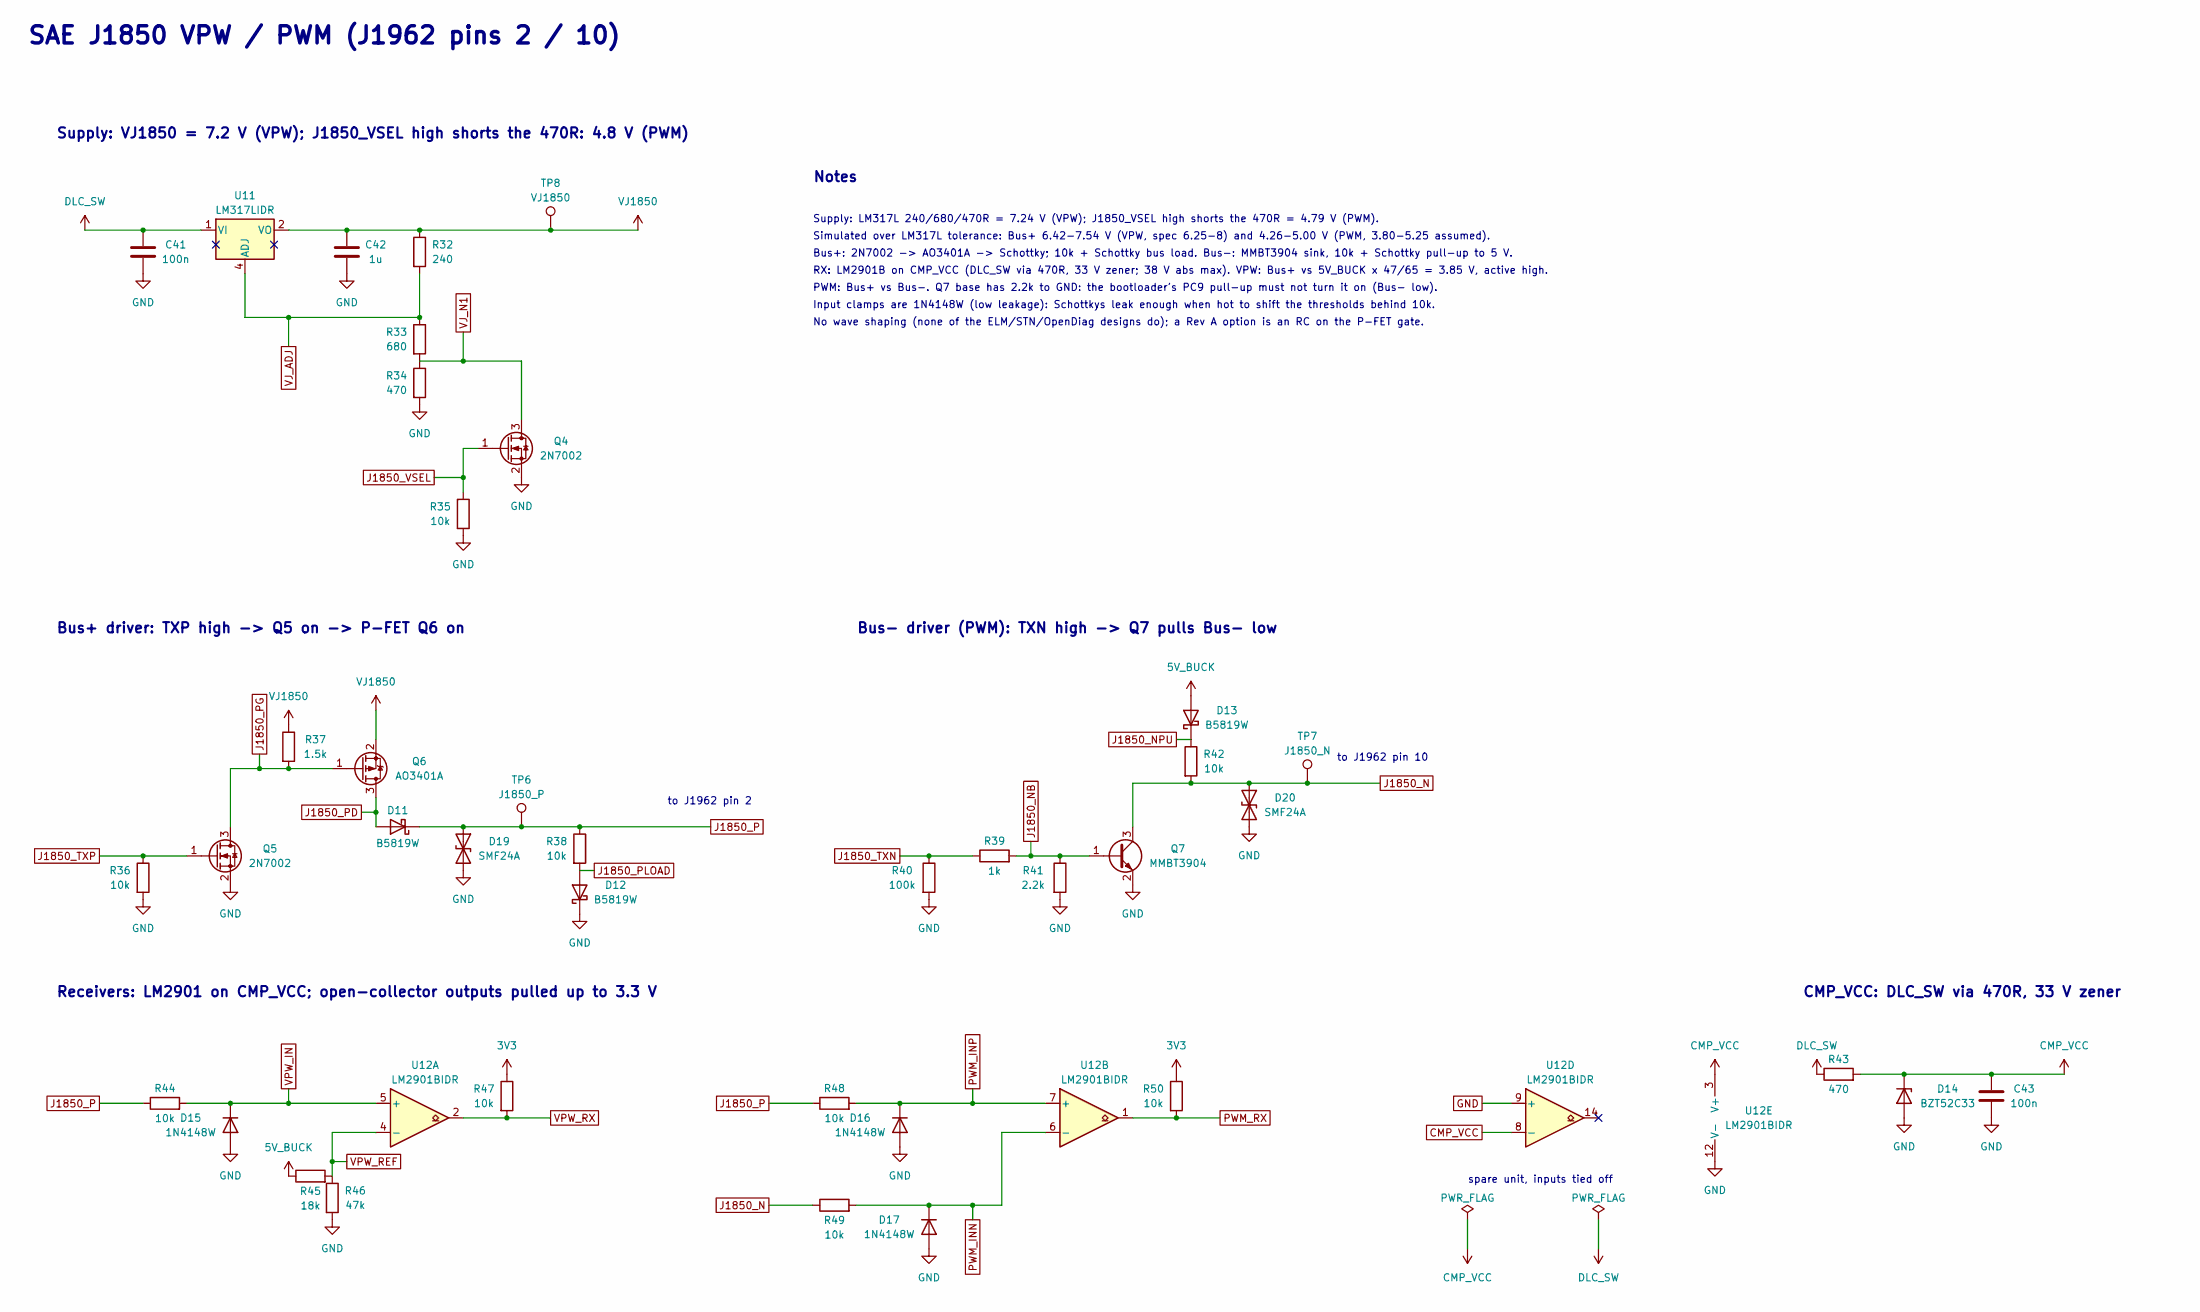
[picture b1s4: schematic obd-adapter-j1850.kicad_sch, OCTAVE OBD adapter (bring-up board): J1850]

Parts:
C41, C43: 100n; C_0603_1608Metric; LCSC C14663
C42: 1u; C_0603_1608Metric; LCSC C15849
D11, D12, D13: B5819W; D_SOD-123; LCSC C8598
D14: BZT52C33; D_SOD-123; LCSC C173417
D15, D16, D17: 1N4148W; D_SOD-123; LCSC C81598
D19, D20: SMF24A; D_SOD-123F; LCSC C19077514
Q4, Q5: 2N7002; SOT-23; LCSC C8545
Q6: AO3401A; SOT-23; LCSC C15127
Q7: MMBT3904; SOT-23; LCSC C20526
R32: 240; R_0603_1608Metric; LCSC C23350
R33: 680; R_0603_1608Metric; LCSC C23228
R34: 470; R_0603_1608Metric; LCSC C23179
R35, R36, R38, R42, R44, R47, R48, R49, R50: 10k; R_0603_1608Metric; LCSC C25804
R37: 1.5k; R_0603_1608Metric; LCSC C22843
R39: 1k; R_0603_1608Metric; LCSC C21190
R40: 100k; R_0603_1608Metric; LCSC C25803
R41: 2.2k; R_0603_1608Metric; LCSC C4190
R43: 470; R_1206_3216Metric; LCSC C4502
R45: 18k; R_0603_1608Metric; LCSC C25810
R46: 47k; R_0603_1608Metric; LCSC C25819
TP6: J1850_P; TestPoint_Pad_D1.5mm
TP7: J1850_N; TestPoint_Pad_D1.5mm
TP8: VJ1850; TestPoint_Pad_D1.5mm
U11: LM317LIDR; SOIC-8_3.9x4.9mm_P1.27mm; LCSC C183332
U12: LM2901BIDR; SOIC-14_3.9x8.7mm_P1.27mm; LCSC C22427890

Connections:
3V3: R47.1, R50.1; also elsewhere on the board
5V_BUCK: D13.2 (A), R45.1; also elsewhere on the board
CMP_VCC: C43.1, D14.1 (K), R43.2, U12.3 (V+), U12.8 (-)
DLC_SW: C41.1, R43.1, U11.1 (VI); also elsewhere on the board
GND: C41.2, C42.2, C43.2, D12.1 (K), D14.2 (A), D15.2 (A), D16.2 (A), D17.2 (A), D19.2 (A2), D20.2 (A2), Q4.2 (S), Q5.2 (S), Q7.2 (E), R34.2, R35.2, R36.2, R40.2, R41.2, R46.2, U12.9 (+), U12.12 (V-); also elsewhere on the board
J1850_N: D20.1 (A1), Q7.3 (C), R42.2, R49.1, TP7.1; also elsewhere on the board
J1850_NB: Q7.1 (B), R39.2, R41.1
J1850_NPU: D13.1 (K), R42.1
J1850_P: D11.1 (K), D19.1 (A1), R38.1, R44.1, R48.1, TP6.1; also elsewhere on the board
J1850_PD: D11.2 (A), Q6.3 (D)
J1850_PG: Q5.3 (D), Q6.1 (G), R37.2
J1850_PLOAD: D12.2 (A), R38.2
J1850_TXN: R39.1, R40.1; also elsewhere on the board
J1850_TXP: Q5.1 (G), R36.1; also elsewhere on the board
J1850_VSEL: Q4.1 (G), R35.1; also elsewhere on the board
PWM_INN: D17.1 (K), R49.2, U12.6 (-)
PWM_INP: D16.1 (K), R48.2, U12.7 (+)
PWM_RX: R50.2, U12.1; also elsewhere on the board
VJ1850: C42.1, Q6.2 (S), R32.1, R37.1, TP8.1, U11.2 (VO), U11.3 (VO), U11.6 (VO), U11.7 (VO)
VJ_ADJ: R32.2, R33.1, U11.4 (ADJ)
VJ_N1: Q4.3 (D), R33.2, R34.1
VPW_IN: D15.1 (K), R44.2, U12.5 (+)
VPW_REF: R45.2, R46.1, U12.4 (-)
VPW_RX: R47.2, U12.2; also elsewhere on the board

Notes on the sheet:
SAE J1850 VPW / PWM (J1962 pins 2 / 10)
Supply: VJ1850 = 7.2 V (VPW); J1850_VSEL high shorts the 470R: 4.8 V (PWM)
Bus+ driver: TXP high -> Q5 on -> P-FET Q6 on
to J1962 pin 2
Bus- driver (PWM): TXN high -> Q7 pulls Bus- low
to J1962 pin 10
Receivers: LM2901 on CMP_VCC; open-collector outputs pulled up to 3.3 V
spare unit, inputs tied off
CMP_VCC: DLC_SW via 470R, 33 V zener
Notes
Supply: LM317L 240/680/470R = 7.24 V (VPW); J1850_VSEL high shorts the 470R = 4.79 V (PWM).
Simulated over LM317L tolerance: Bus+ 6.42-7.54 V (VPW, spec 6.25-8) and 4.26-5.00 V (PWM, 3.80-5.25 assumed).
Bus+: 2N7002 -> AO3401A -> Schottky; 10k + Schottky bus load. Bus-: MMBT3904 sink, 10k + Schottky pull-up to 5 V.
RX: LM2901B on CMP_VCC (DLC_SW via 470R, 33 V zener; 38 V abs max). VPW: Bus+ vs 5V_BUCK x 47/65 = 3.85 V, active high.
PWM: Bus+ vs Bus-. Q7 base has 2.2k to GND: the bootloader's PC9 pull-up must not turn it on (Bus- low).
Input clamps are 1N4148W (low leakage): Schottkys leak enough when hot to shift the thresholds behind 10k.
No wave shaping (none of the ELM/STN/OpenDiag designs do); a Rev A option is an RC on the P-FET gate.

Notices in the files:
README.md:
License: GPL v3+
